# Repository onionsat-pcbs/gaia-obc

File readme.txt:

Kicadben az outline importálása: File -> Import -> Graphics

import scale: 1
dxf defult line width: 0.2mm
dxf defult units: millimetres
place at: x-eld ki
layer: edge cuts
group: kikapcsolva
fix discontinuities: kikapcsolva

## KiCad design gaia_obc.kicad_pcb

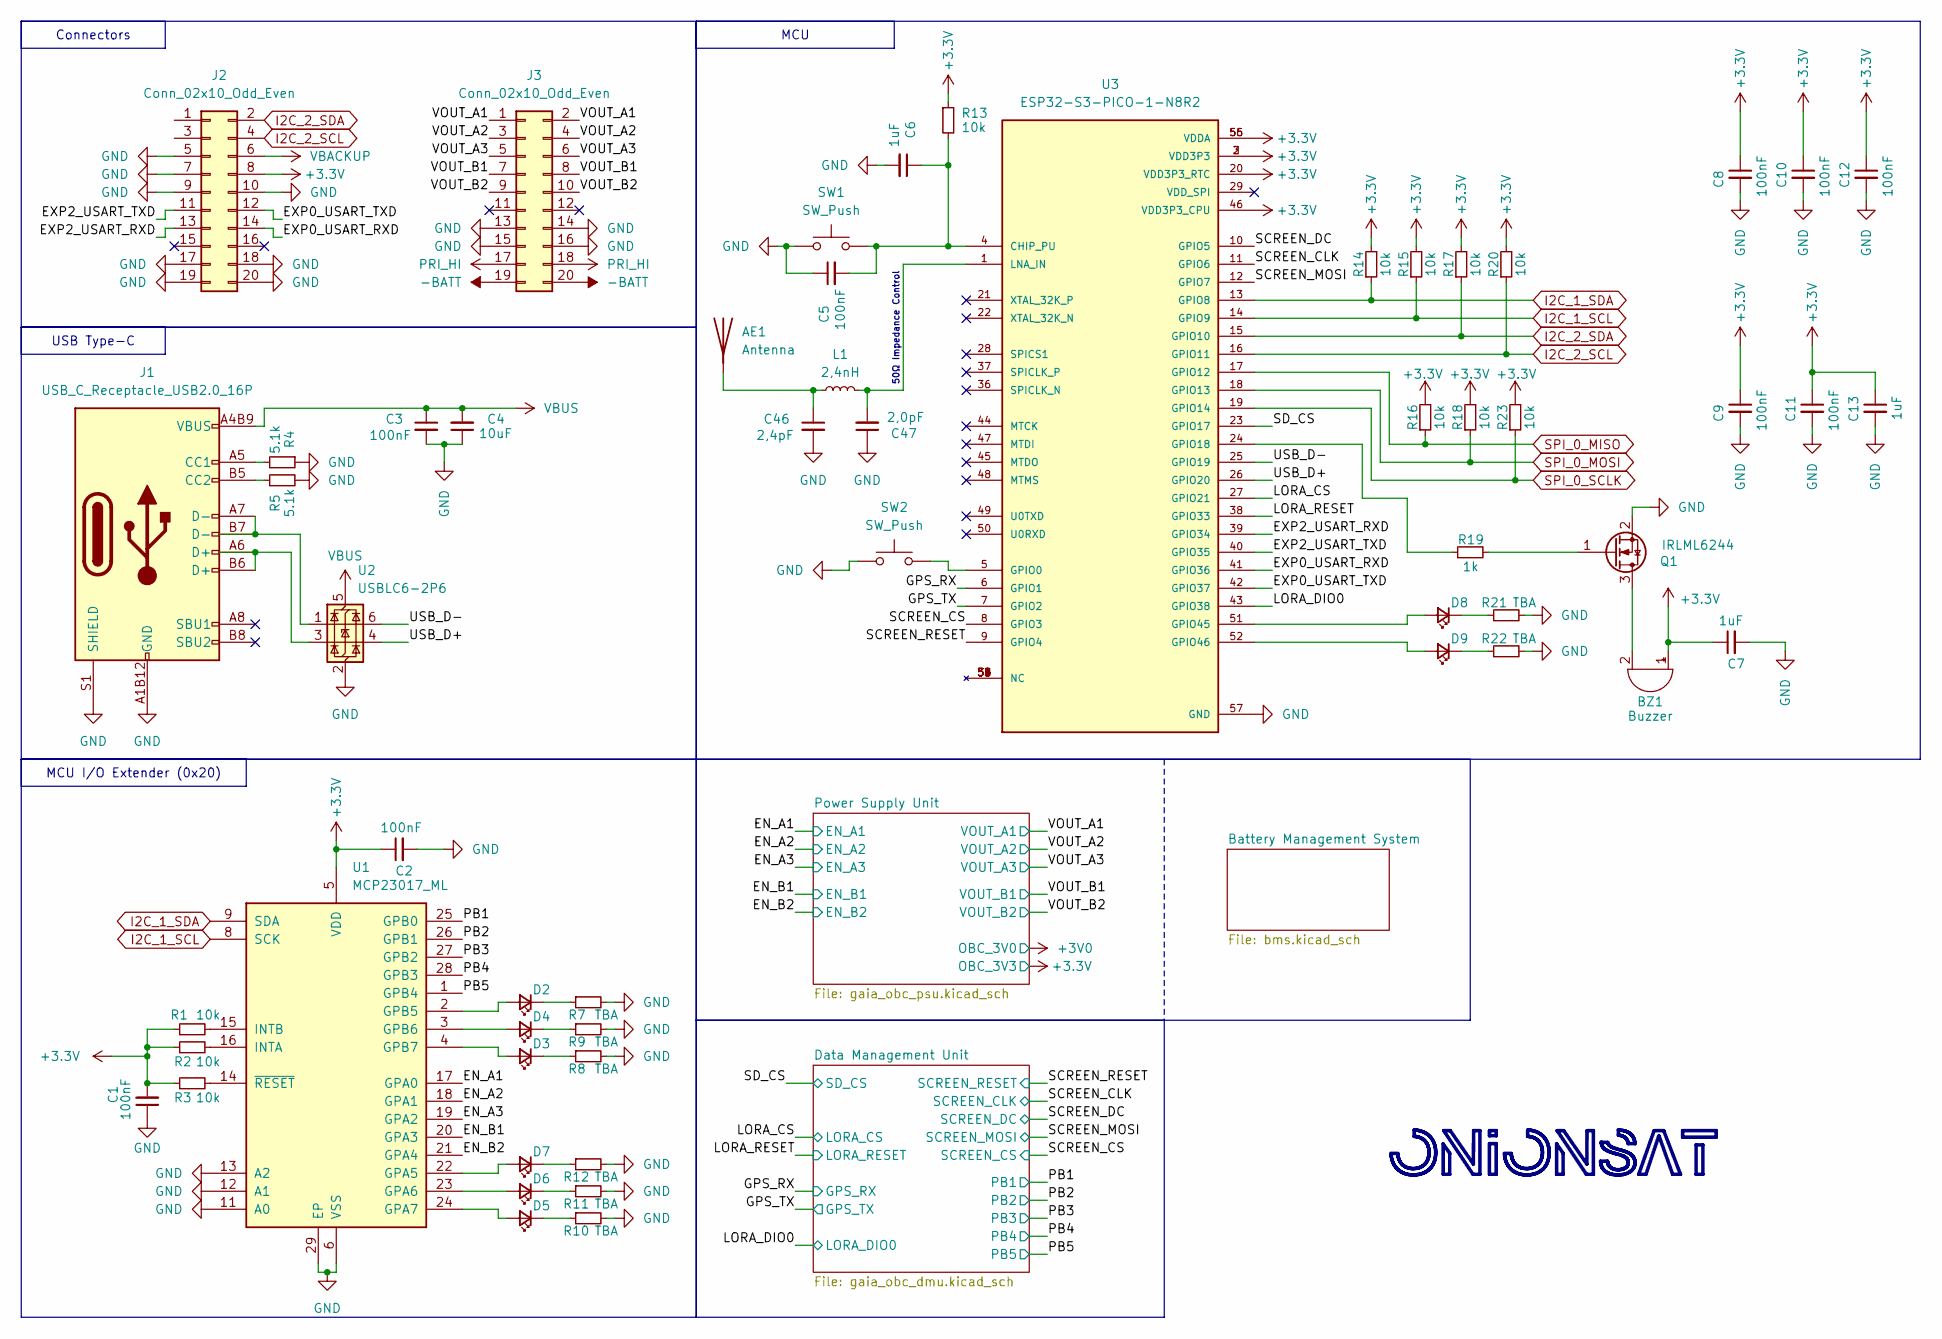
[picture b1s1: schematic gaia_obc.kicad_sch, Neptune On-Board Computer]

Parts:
AE1: Antenna; ANT-SMD_L8.0-W1.0
BZ1: Buzzer; buzzer_MLT-5020
C1, C2, C3, C5, C8, C9, C10, C11, C12: 100nF; C_0402_1005Metric
C4: 10uF; C_0603_1608Metric
C6, C7, C13: 1uF; C_0402_1005Metric
C46: 2,4pF; C_0402_1005Metric
C47: 2,0pF; C_0402_1005Metric
D2, D3, D4, D5, D6, D7, D8, D9: LED_Small; LED_0603_1608Metric
J1: USB_C_Receptacle_USB2.0_16P; USB-SMD_TYPE-C-16PQT-073
J2, J3: Conn_02x10_Odd_Even; PinHeader_2x10_P2.00mm_Vertical_SMD
L1: 2,4nH; L_0402_1005Metric
Q1: IRLML6244; SOT-23
R1, R2, R3, R13, R14, R15, R16, R17, R18, R20, R23: 10k; R_0402_1005Metric
R4, R5: 5.1k; R_0402_1005Metric
R7, R8, R9, R10, R11, R12, R21, R22: TBA; R_0402_1005Metric
R19: 1k; R_0402_1005Metric
SW1, SW2: SW_Push; KEY-SMD_L4.0-W3.0-LS4.9-1
U1: MCP23017_ML; QFN-28-1EP_6x6mm_P0.65mm_EP4.25x4.25mm
U2: USBLC6-2P6; SOT-666
U3: ESP32-S3-PICO-1-N8R2; PQFN40P700X700X106-57N; PARTREV 1.0

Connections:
+3.3V: BZ1.1 (+), C1.2, C2.1, C7.1, C8.1, C9.1, C10.1, C11.1, C12.1, C13.1, J2.8, R1.1, R2.1, R3.1, R13.1, R14.2, R15.2, R16.2, R17.2, R18.2, R20.2, R23.2, U1.5 (VDD), U3.2 (VDD3P3), U3.3 (VDD3P3), U3.20 (VDD3P3_RTC), U3.46 (VDD3P3_CPU), U3.55 (VDDA), U3.56 (VDDA); also elsewhere on the board
-BATT: J3.19, J3.20; also elsewhere on the board
/EN_A1: U1.17 (GPA0); also elsewhere on the board
/EN_A2: U1.18 (GPA1); also elsewhere on the board
/EN_A3: U1.19 (GPA2); also elsewhere on the board
/EN_B1: U1.20 (GPA3); also elsewhere on the board
/EN_B2: U1.21 (GPA4); also elsewhere on the board
/EXP0_USART_RXD: J2.14, U3.41 (GPIO36)
/EXP0_USART_TXD: J2.12, U3.42 (GPIO37)
/EXP2_USART_RXD: J2.13, U3.39 (GPIO34)
/EXP2_USART_TXD: J2.11, U3.40 (GPIO35)
/GPS_RX: U3.6 (GPIO1); also elsewhere on the board
/GPS_TX: U3.7 (GPIO2); also elsewhere on the board
/LORA_CS: U3.27 (GPIO21); also elsewhere on the board
/LORA_DIO0: U3.43 (GPIO38); also elsewhere on the board
/LORA_RESET: U3.38 (GPIO33); also elsewhere on the board
/PB1: U1.25 (GPB0); also elsewhere on the board
/PB2: U1.26 (GPB1); also elsewhere on the board
/PB3: U1.27 (GPB2); also elsewhere on the board
/PB4: U1.28 (GPB3); also elsewhere on the board
/PB5: U1.1 (GPB4); also elsewhere on the board
/SCREEN_CLK: U3.11 (GPIO6); also elsewhere on the board
/SCREEN_CS: U3.8 (GPIO3); also elsewhere on the board
/SCREEN_DC: U3.10 (GPIO5); also elsewhere on the board
/SCREEN_MOSI: U3.12 (GPIO7); also elsewhere on the board
/SCREEN_RESET: U3.9 (GPIO4); also elsewhere on the board
/SD_CS: U3.23 (GPIO17); also elsewhere on the board
/USB_D+: U2.4 (I/O2), U3.26 (GPIO20)
/USB_D-: U2.6 (I/O1), U3.25 (GPIO19)
/VOUT_A1: J3.1, J3.2; also elsewhere on the board
/VOUT_A2: J3.3, J3.4; also elsewhere on the board
/VOUT_A3: J3.5, J3.6; also elsewhere on the board
/VOUT_B1: J3.7, J3.8; also elsewhere on the board
/VOUT_B2: J3.9, J3.10; also elsewhere on the board
GND: C1.1, C2.2, C3.2, C4.1, C5.1, C6.2, C7.2, C8.2, C9.2, C10.2, C11.2, C12.2, C13.2, C46.2, C47.1, J1.A1B12 (GND), J1.B1A12 (GND), J1.S1 (SHIELD), J2.5, J2.7, J2.9, J2.10, J2.17, J2.18, J2.19, J2.20, J3.13, J3.14, J3.15, J3.16, Q1.2 (S), R4.1, R5.2, R7.2, R8.2, R9.2, R10.2, R11.2, R12.2, R21.2, R22.2, SW1.1, SW2.1, U1.6 (VSS), U1.11 (A0), U1.12 (A1), U1.13 (A2), U1.29 (EP), U2.2 (GND), U3.57 (GND); also elsewhere on the board
I2C_1_SCL: R15.1, U1.8 (SCK), U3.14 (GPIO9); also elsewhere on the board
I2C_1_SDA: R14.1, U1.9 (SDA), U3.13 (GPIO8); also elsewhere on the board
I2C_2_SCL: J2.4, R20.1, U3.16 (GPIO11)
I2C_2_SDA: J2.2, R17.1, U3.15 (GPIO10)
unnamed: AE1.1 (A), C46.1, L1.1
unnamed: BZ1.2 (-), Q1.3 (D)
unnamed: D2.2 (A), U1.2 (GPB5)
unnamed: D2.1 (K), R7.1
unnamed: D3.2 (A), U1.4 (GPB7)
unnamed: D3.1 (K), R8.1
unnamed: D4.2 (A), U1.3 (GPB6)
unnamed: D4.1 (K), R9.1
unnamed: D5.2 (A), U1.24 (GPA7)
unnamed: D5.1 (K), R10.1
unnamed: D6.2 (A), U1.23 (GPA6)
unnamed: D6.1 (K), R11.1
unnamed: D7.2 (A), U1.22 (GPA5)
unnamed: D7.1 (K), R12.1
unnamed: D8.2 (A), U3.51 (GPIO45)
unnamed: D8.1 (K), R21.1
unnamed: D9.2 (A), U3.52 (GPIO46)
unnamed: D9.1 (K), R22.1
unnamed: J1.A5 (CC1), R4.2
unnamed: J1.B5 (CC2), R5.1
unnamed: J1.A6 (D+), J1.B6 (D+), U2.3 (I/O2)
unnamed: J1.A7 (D-), J1.B7 (D-), U2.1 (I/O1)
unnamed: Q1.1 (G), R19.2
unnamed: R2.2, U1.16 (INTA)
unnamed: R1.2, U1.15 (INTB)
unnamed: R3.2, U1.14 (~RESET)
unnamed: C5.2, C6.1, R13.2, SW1.2, U3.4 (CHIP_PU)
unnamed: SW2.2, U3.5 (GPIO0)
unnamed: R19.1, U3.24 (GPIO18)
unnamed: C47.2, L1.2, U3.1 (LNA_IN)
PRI_HI: J3.17, J3.18; also elsewhere on the board
SPI_0_MISO: R16.1, U3.17 (GPIO12); also elsewhere on the board
SPI_0_MOSI: R18.1, U3.18 (GPIO13); also elsewhere on the board
SPI_0_SCLK: R23.1, U3.19 (GPIO14); also elsewhere on the board
VBACKUP: J2.6; also elsewhere on the board
VBUS: C3.1, C4.2, J1.A4B9 (VBUS), J1.B4A9 (VBUS), U2.5 (VBUS); also elsewhere on the board

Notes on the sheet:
50Ω Impedance Control
USB Type-C
Connectors
MCU
MCU I/O Extender (0x20)

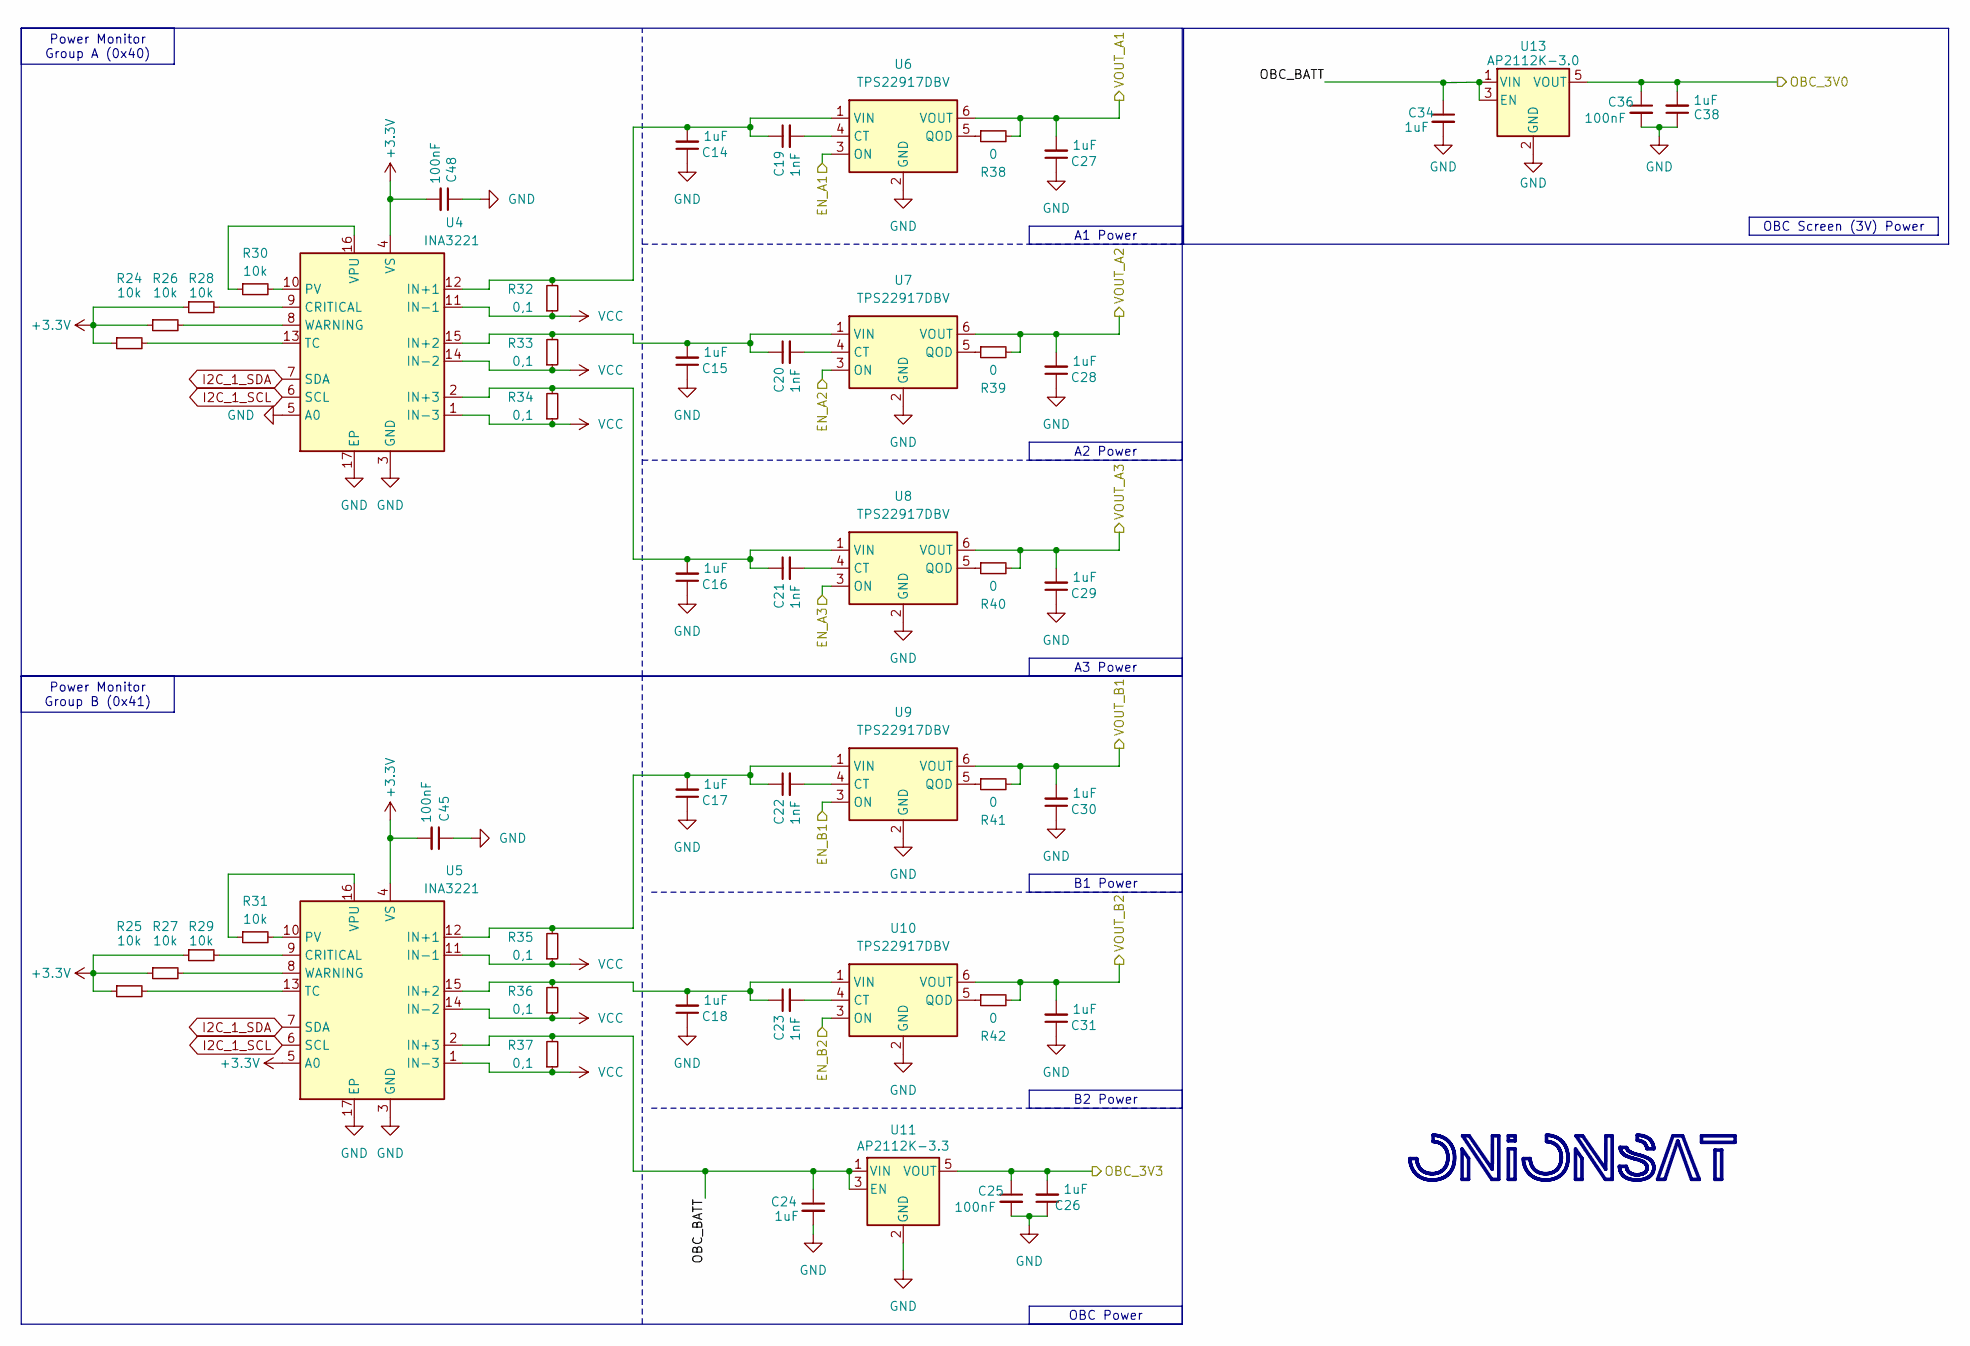
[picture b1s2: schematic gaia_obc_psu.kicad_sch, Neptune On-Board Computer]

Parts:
C14, C15, C16, C17, C18, C24, C26, C27, C28, C29, C30, C31, C34, C38: 1uF; C_0402_1005Metric
C19, C20, C21, C22, C23: 1nF; C_0402_1005Metric
C25, C36, C45, C48: 100nF; C_0402_1005Metric
R24, R25, R26, R27, R28, R29, R30, R31: 10k; R_0402_1005Metric
R32, R33, R34, R35, R36, R37: 0,1; R_1206_3216Metric
R38, R39, R40, R41, R42: 0; R_0402_1005Metric
U4, U5: INA3221; Texas_RGV0016A_VQFN-16-1EP_4x4mm_P0.65mm_EP2.1x2.1mm
U6, U7, U8, U9, U10: TPS22917DBV; SOT-23-6
U11: AP2112K-3.3; SOT-23-5
U13: AP2112K-3.0; SOT-23-5

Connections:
+3.3V: C25.1, C26.2, C45.2, C48.2, R24.1, R25.1, R26.1, R27.1, R28.1, R29.1, U4.4 (VS), U5.4 (VS), U5.5 (A0), U11.5 (VOUT); also elsewhere on the board
+3V0: C36.1, C38.2, U13.5 (VOUT); also elsewhere on the board
/EN_A1: U6.3 (ON); also elsewhere on the board
/EN_A2: U7.3 (ON); also elsewhere on the board
/EN_A3: U8.3 (ON); also elsewhere on the board
/EN_B1: U9.3 (ON); also elsewhere on the board
/EN_B2: U10.3 (ON); also elsewhere on the board
/Power Supply Unit/OBC_BATT: C24.1, C34.1, R37.2, U5.2 (IN+3), U11.1 (VIN), U11.3 (EN), U13.1 (VIN), U13.3 (EN)
/VOUT_A1: C27.2, R38.2, U6.6 (VOUT); also elsewhere on the board
/VOUT_A2: C28.2, R39.2, U7.6 (VOUT); also elsewhere on the board
/VOUT_A3: C29.2, R40.2, U8.6 (VOUT); also elsewhere on the board
/VOUT_B1: C30.2, R41.2, U9.6 (VOUT); also elsewhere on the board
/VOUT_B2: C31.2, R42.2, U10.6 (VOUT); also elsewhere on the board
GND: C14.1, C15.1, C16.1, C17.1, C18.1, C24.2, C25.2, C26.1, C27.1, C28.1, C29.1, C30.1, C31.1, C34.2, C36.2, C38.1, C45.1, C48.1, U4.3 (GND), U4.5 (A0), U4.17 (EP), U5.3 (GND), U5.17 (EP), U6.2 (GND), U7.2 (GND), U8.2 (GND), U9.2 (GND), U10.2 (GND), U11.2 (GND), U13.2 (GND); also elsewhere on the board
I2C_1_SCL: U4.6 (SCL), U5.6 (SCL); also elsewhere on the board
I2C_1_SDA: U4.7 (SDA), U5.7 (SDA); also elsewhere on the board
unnamed: R28.2, U4.9 (CRITICAL)
unnamed: C14.2, C19.1, R32.2, U4.12 (IN+1), U6.1 (VIN)
unnamed: C15.2, C20.1, R33.2, U4.15 (IN+2), U7.1 (VIN)
unnamed: C16.2, C21.1, R34.2, U4.2 (IN+3), U8.1 (VIN)
unnamed: R30.2, U4.10 (PV)
unnamed: R24.2, U4.13 (TC)
unnamed: R30.1, U4.16 (VPU)
unnamed: R26.2, U4.8 (WARNING)
unnamed: R29.2, U5.9 (CRITICAL)
unnamed: C17.2, C22.1, R35.2, U5.12 (IN+1), U9.1 (VIN)
unnamed: R31.2, U5.10 (PV)
unnamed: R25.2, U5.13 (TC)
unnamed: R31.1, U5.16 (VPU)
unnamed: R27.2, U5.8 (WARNING)
unnamed: C19.2, U6.4 (CT)
unnamed: R38.1, U6.5 (QOD)
unnamed: C20.2, U7.4 (CT)
unnamed: R39.1, U7.5 (QOD)
unnamed: C21.2, U8.4 (CT)
unnamed: R40.1, U8.5 (QOD)
unnamed: C22.2, U9.4 (CT)
unnamed: R41.1, U9.5 (QOD)
unnamed: C23.2, U10.4 (CT)
unnamed: R42.1, U10.5 (QOD)
unnamed: C18.2, C23.1, R36.2, U5.15 (IN+2), U10.1 (VIN)
VCC: R32.1, R33.1, R34.1, R35.1, R36.1, R37.1, U4.1 (IN-3), U4.11 (IN-1), U4.14 (IN-2), U5.1 (IN-3), U5.11 (IN-1), U5.14 (IN-2); also elsewhere on the board

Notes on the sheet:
A2 Power
A1 Power
B1 Power
OBC Power
Power Monitor Group A (0x40)
OBC Screen (3V) Power
B2 Power
A3 Power
Power Monitor Group B (0x41)

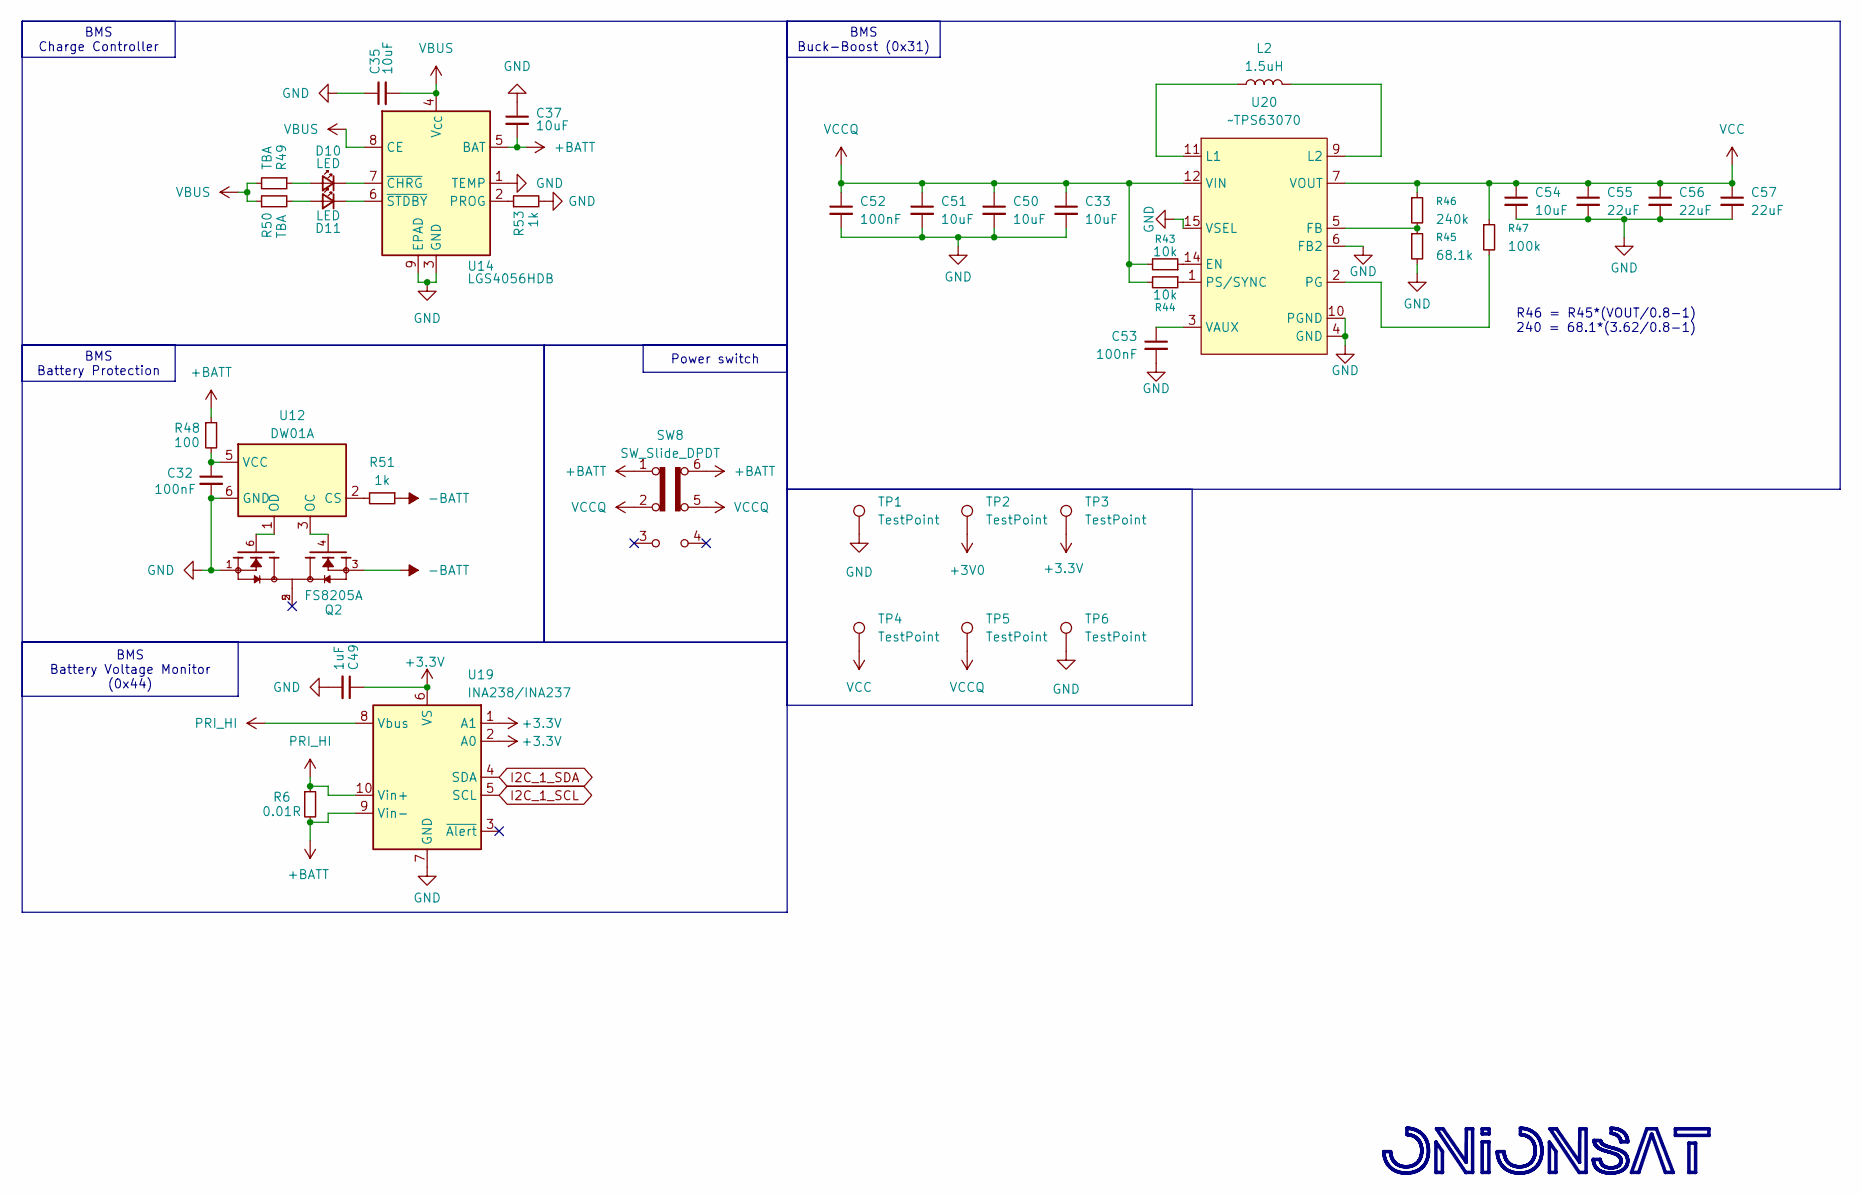
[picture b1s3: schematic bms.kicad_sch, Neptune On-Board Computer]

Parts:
C32: 100nF; C_0402_1005Metric
C33, C35, C37, C54: 10uF; C_0603_1608Metric
C49: 1uF; C_0603_1608Metric
C50, C51: 10uF; C_0805_2012Metric
C52, C53: 100nF; C_0603_1608Metric
C55, C56, C57: 22uF; C_0805_2012Metric
D10, D11: LED; LED_0805_2012Metric
L2: 1.5uH; XFL4020152MEC
Q2: FS8205A; SOT-23-6; PARTREV 1.7
R6: 0.01R; R_2512_6332Metric
R43, R44: 10k; R_0402_1005Metric
R45: 68.1k; R_0603_1608Metric
R46: 240k; R_0603_1608Metric
R47: 100k; R_0603_1608Metric
R48: 100; R_0603_1608Metric
R49, R50: TBA; R_0603_1608Metric
R51: 1k; R_0603_1608Metric
R53: 1k; R_0402_1005Metric
SW8: SW_Slide_DPDT; MS-22D28-G020
TP1, TP2, TP3, TP4, TP5, TP6: TestPoint; TestPoint_Pad_1.0x1.0mm
U12: DW01A; SOT-23-6
U14: LGS4056HDB; DFN-8-1EP_3x3mm_P0.65mm_EP1.55x2.4mm
U19: INA238/INA237; VSSOP-10_3x3mm_P0.5mm
U20: ~TPS63070; TPS630701RNMR

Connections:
+3.3V: C49.1, TP3.1, U19.1 (A1), U19.2 (A0), U19.6 (VS); also elsewhere on the board
+3V0: TP2.1; also elsewhere on the board
+BATT: C37.2, R6.2, R48.1, SW8.1 (A), SW8.6 (C), U14.5 (BAT), U19.9 (Vin-)
-BATT: Q2.3, R51.1; also elsewhere on the board
GND: C32.2, C33.2, C35.1, C37.1, C49.2, C50.2, C51.2, C52.2, C53.2, C54.2, C55.2, C56.2, C57.2, Q2.1, R45.2, R53.2, TP1.1, TP6.1, U12.6 (GND), U14.1 (TEMP), U14.3 (GND), U14.9 (EPAD), U19.7 (GND), U20.4 (GND), U20.6 (FB2), U20.10 (PGND), U20.15 (VSEL); also elsewhere on the board
I2C_1_SCL: U19.5 (SCL); also elsewhere on the board
I2C_1_SDA: U19.4 (SDA); also elsewhere on the board
unnamed: D10.2 (A), R49.1
unnamed: D10.1 (K), U14.7 (~CHRG)
unnamed: D11.2 (A), R50.2
unnamed: D11.1 (K), U14.6 (~STDBY)
unnamed: R51.2, U12.2 (CS)
unnamed: Q2.4, U12.3 (OC)
unnamed: Q2.6, U12.1 (OD)
unnamed: C32.1, R48.2, U12.5 (VCC)
unnamed: R53.1, U14.2 (PROG)
unnamed: R43.1, U20.14 (EN)
unnamed: R45.1, R46.2, U20.5 (FB)
unnamed: L2.1, U20.11 (L1)
unnamed: L2.2, U20.9 (L2)
unnamed: R47.2, U20.2 (PG)
unnamed: R44.1, U20.1 (PS/SYNC)
unnamed: C53.1, U20.3 (VAUX)
PRI_HI: R6.1, U19.8 (Vbus), U19.10 (Vin+); also elsewhere on the board
VBUS: C35.2, R49.2, R50.1, U14.4 (V_{CC}), U14.8 (CE); also elsewhere on the board
VCC: C54.1, C55.1, C56.1, C57.1, R46.1, R47.1, TP4.1, U20.7 (VOUT); also elsewhere on the board
VCCQ: C33.1, C50.1, C51.1, C52.1, R43.2, R44.2, SW8.2 (B), SW8.5 (B), TP5.1, U20.12 (VIN)

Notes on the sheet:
R46 = R45*(VOUT/0.8-1) 240 = 68.1*(3.62/0.8-1)
BMS Buck-Boost (0x31)
BMS Charge Controller
BMS Battery Voltage Monitor (0x44)
Power switch
BMS Battery Protection

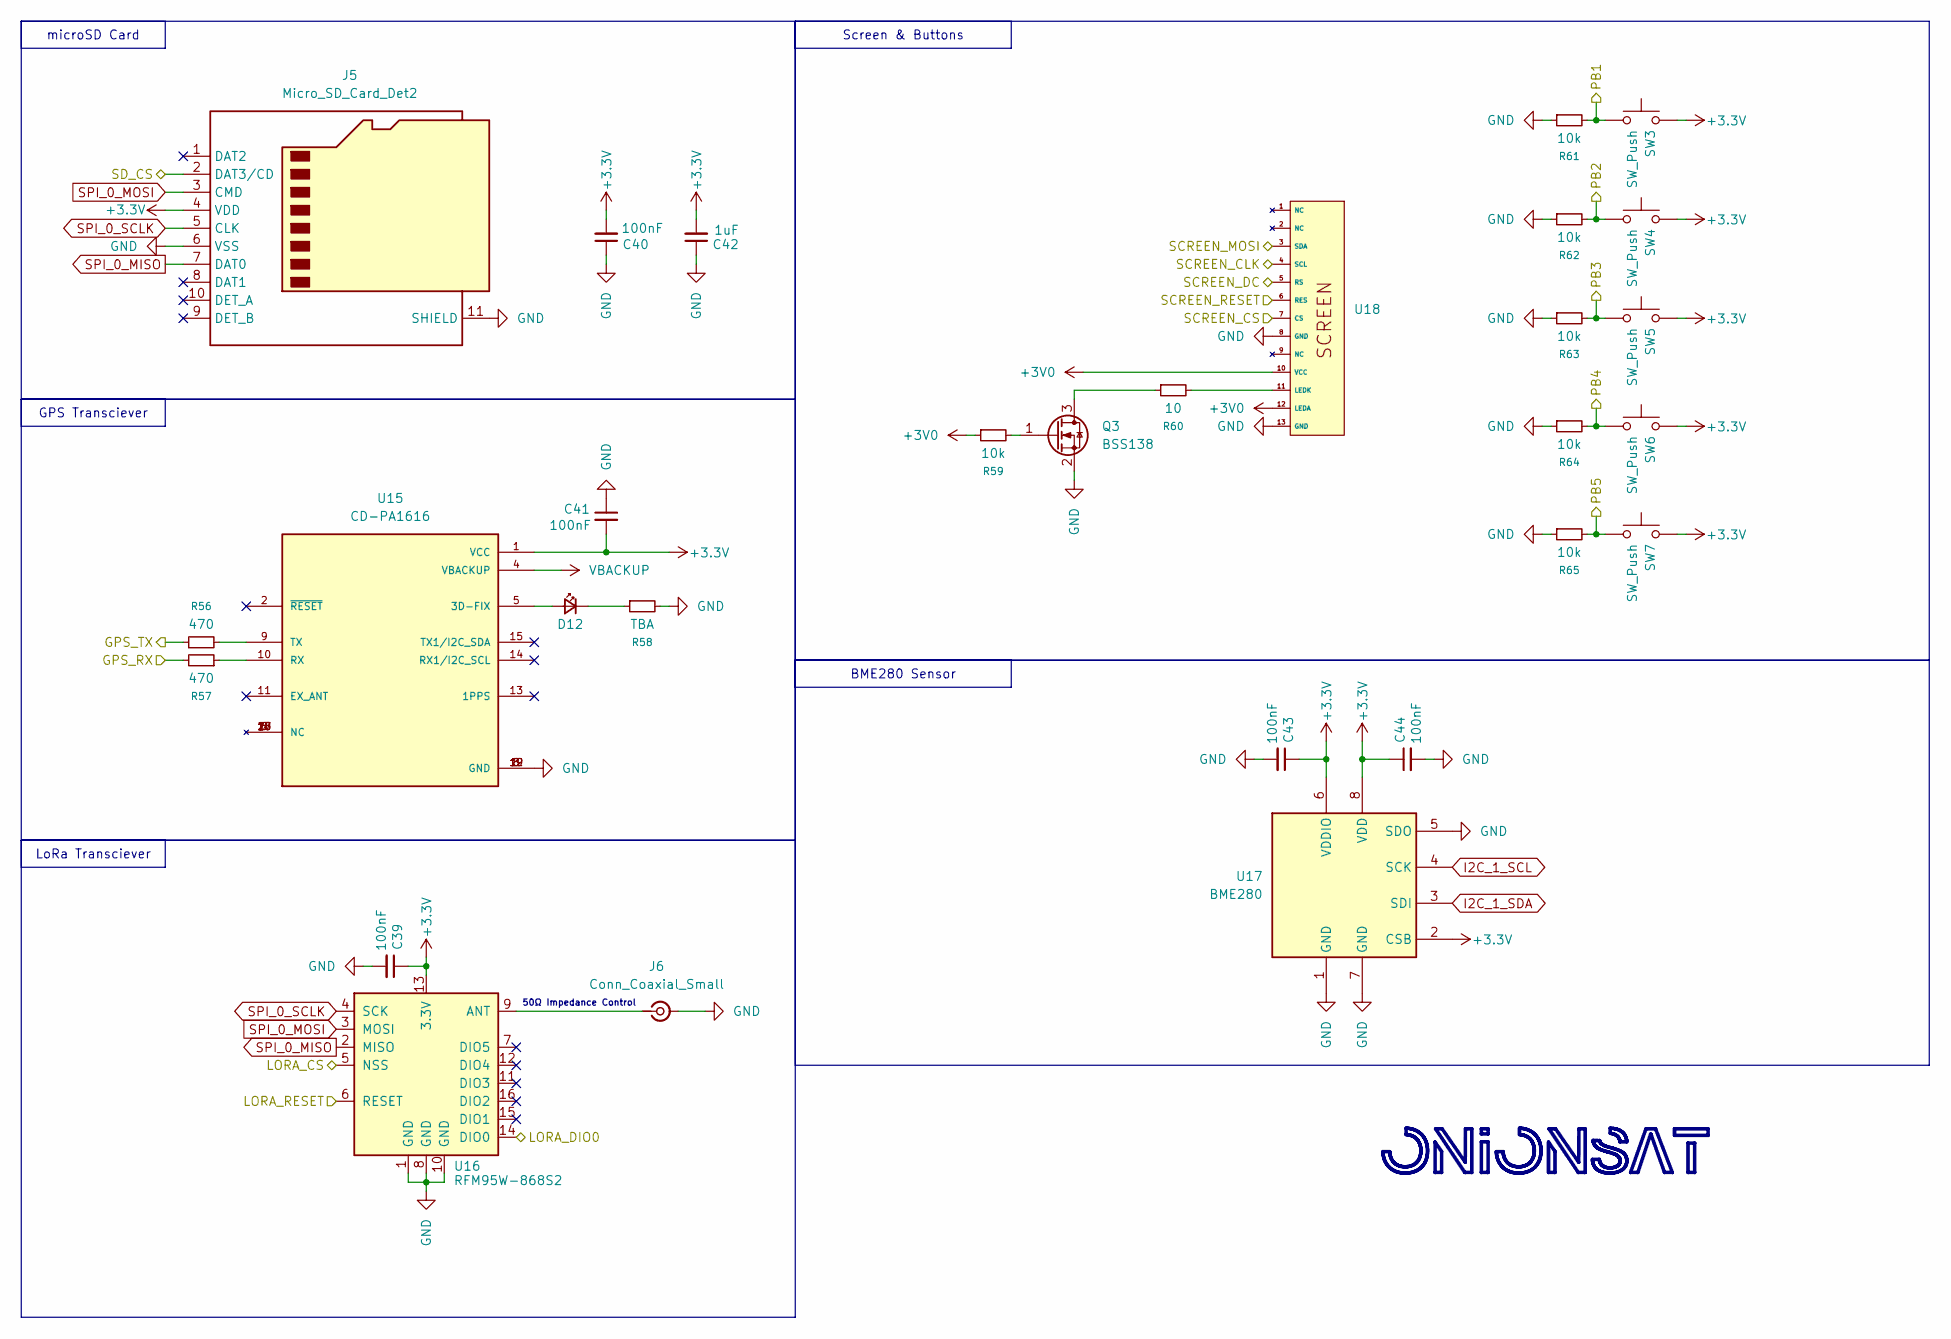
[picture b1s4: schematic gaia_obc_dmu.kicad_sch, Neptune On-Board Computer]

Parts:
C39, C40, C41, C43, C44: 100nF; C_0402_1005Metric
C42: 1uF; C_0402_1005Metric
D12: LED_Small; LED_0603_1608Metric
J5: Micro_SD_Card_Det2; microSD_HC_Hirose_DM3D-SF
J6: Conn_Coaxial_Small; U.FL_Hirose_U.FL-R-SMT-1_Vertical
Q3: BSS138; SOT-23
R56, R57: 470; R_0402_1005Metric
R58: TBA; R_0402_1005Metric
R59, R61, R62, R63, R64, R65: 10k; R_0402_1005Metric
R60: 10; R_0603_1608Metric
SW3, SW4, SW5, SW6, SW7: SW_Push; KEY-SMD_4P-L3.1-W3.1-P2.00-LS4.0
U15: CD-PA1616; XCVR_CD-PA1616D; PARTREV V.06
U16: RFM95W-868S2; HOPERF_RFM9XW_SMD
U17: BME280; Bosch_LGA-8_2.5x2.5mm_P0.65mm_ClockwisePinNumbering
U18: OLED-SMD_ST7735S

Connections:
+3.3V: C39.1, C40.2, C41.2, C42.2, C43.1, C44.1, J5.4 (VDD), SW3.2, SW4.2, SW5.2, SW6.2, SW7.2, U15.1 (VCC), U16.13 (3.3V), U17.2 (CSB), U17.6 (VDDIO), U17.8 (VDD); also elsewhere on the board
+3V0: R59.1, U18.10 (VCC), U18.12 (LEDA); also elsewhere on the board
/GPS_RX: R57.2; also elsewhere on the board
/GPS_TX: R56.1; also elsewhere on the board
/LORA_CS: U16.5 (NSS); also elsewhere on the board
/LORA_DIO0: U16.14 (DIO0); also elsewhere on the board
/LORA_RESET: U16.6 (RESET); also elsewhere on the board
/PB1: R61.2, SW3.1; also elsewhere on the board
/PB2: R62.2, SW4.1; also elsewhere on the board
/PB3: R63.2, SW5.1; also elsewhere on the board
/PB4: R64.2, SW6.1; also elsewhere on the board
/PB5: R65.2, SW7.1; also elsewhere on the board
/SCREEN_CLK: U18.4 (SCL); also elsewhere on the board
/SCREEN_CS: U18.7 (CS); also elsewhere on the board
/SCREEN_DC: U18.5 (RS); also elsewhere on the board
/SCREEN_MOSI: U18.3 (SDA); also elsewhere on the board
/SCREEN_RESET: U18.6 (RES); also elsewhere on the board
/SD_CS: J5.2 (DAT3/CD); also elsewhere on the board
GND: C39.2, C40.1, C41.1, C42.1, C43.2, C44.2, J5.6 (VSS), J5.11 (SHIELD), J6.2 (Ext), Q3.2 (S), R58.2, R61.1, R62.1, R63.1, R64.1, R65.1, U15.3 (GND), U15.8 (GND), U15.12 (GND), U15.19 (GND), U16.1 (GND), U16.8 (GND), U16.10 (GND), U17.1 (GND), U17.5 (SDO), U17.7 (GND), U18.8 (GND), U18.13 (GND); also elsewhere on the board
I2C_1_SCL: U17.4 (SCK); also elsewhere on the board
I2C_1_SDA: U17.3 (SDI); also elsewhere on the board
unnamed: D12.2 (A), U15.5 (3D-FIX)
unnamed: D12.1 (K), R58.1
unnamed: J6.1 (In), U16.9 (ANT)
unnamed: Q3.3 (D), R60.1
unnamed: Q3.1 (G), R59.2
unnamed: R57.1, U15.10 (RX)
unnamed: R56.2, U15.9 (TX)
unnamed: R60.2, U18.11 (LEDK)
SPI_0_MISO: J5.7 (DAT0), U16.2 (MISO); also elsewhere on the board
SPI_0_MOSI: J5.3 (CMD), U16.3 (MOSI); also elsewhere on the board
SPI_0_SCLK: J5.5 (CLK), U16.4 (SCK); also elsewhere on the board
VBACKUP: U15.4 (VBACKUP); also elsewhere on the board

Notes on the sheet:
50Ω Impedance Control
Screen & Buttons
BME280 Sensor
microSD Card
GPS Transciever
LoRa Transciever

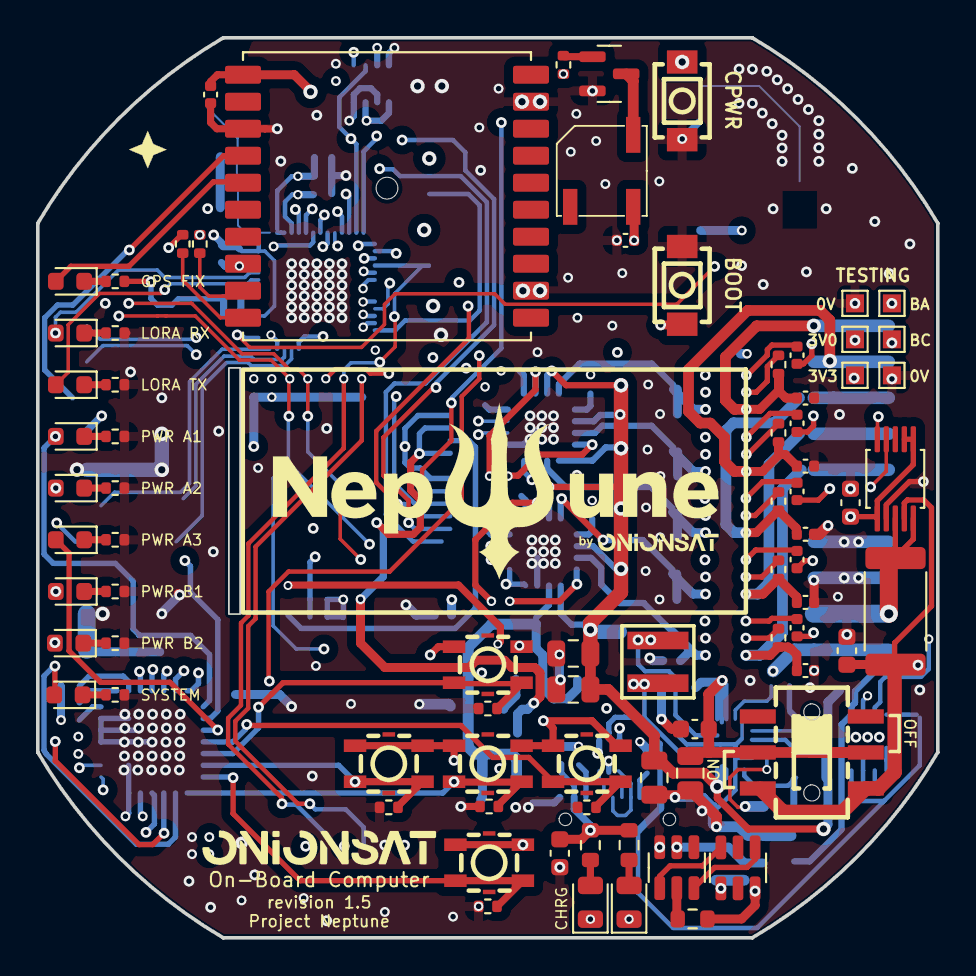
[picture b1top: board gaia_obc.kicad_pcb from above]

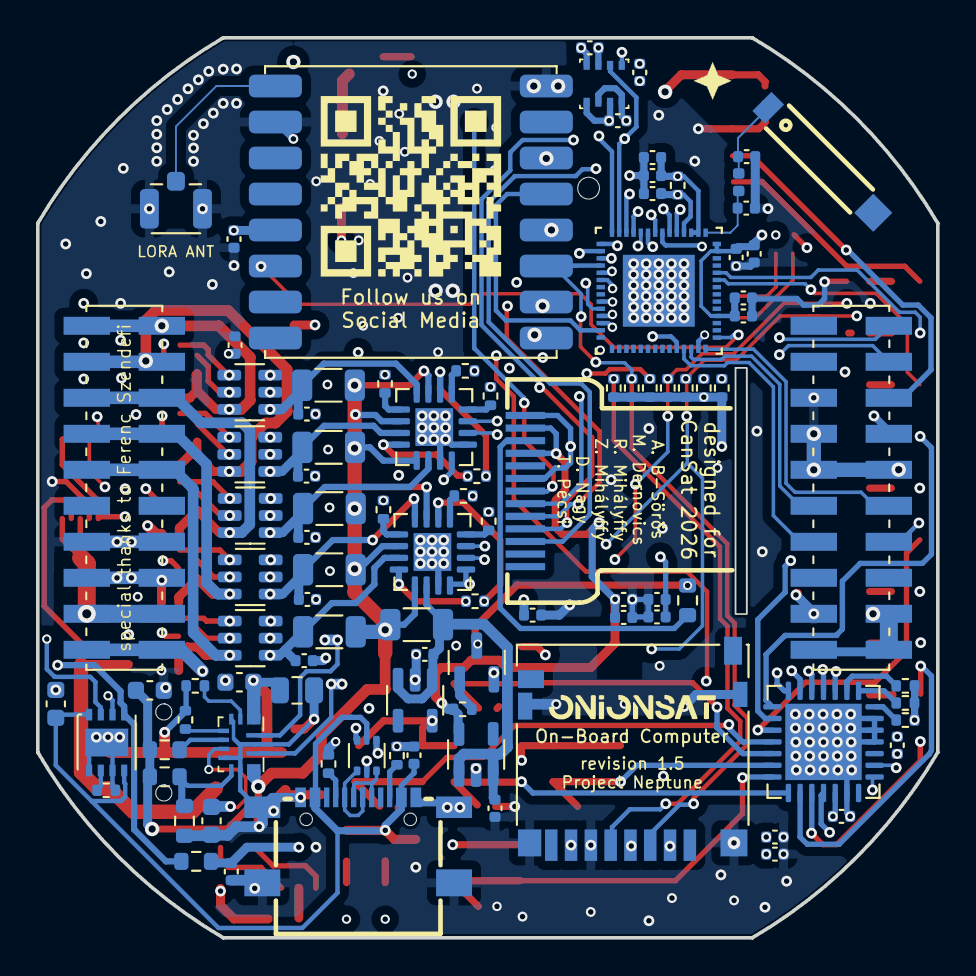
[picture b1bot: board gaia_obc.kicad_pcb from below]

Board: 8 copper layers, 50.0 x 50.0 mm, 176 parts (97 on the bottom side), 129 nets.
